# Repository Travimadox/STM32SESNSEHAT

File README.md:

# Imperium Environmental Monitoring HAT

The Imperium Environmental Monitoring HAT is a cutting-edge hardware accessory designed for use with STM32 microcontrollers. It is tailored for environmental monitoring and equipped with high-precision sensors for temperature and light. This allows for accurate data collection in various applications, including weather monitoring, room temperature monitoring, and greenhouse monitoring, providing invaluable insights into environmental conditions.

## Features

- High-precision sensors for temperature, humidity, atmospheric pressure, and light
- Seamlessly integrates into various systems
- Customizable to fit the needs of each user
- Easily programmable for extra functionality
- Affordable and reliable

## Usage

The Imperium Environmental Monitoring HAT can be used for a variety of purposes, including:

- Weather monitoring
- Room temperature and humidity monitoring
- Greenhouse monitoring

In addition, the sensor data can be used to make critical decisions about controlling external devices, such as triggering a fan or heater, to maintain a comfortable environment.

## Getting Started

To get started with the Imperium Environmental Monitoring HAT, simply connect it to your STM32 microcontroller using the provided pins. Then, download our library and follow the included instructions to begin collecting data.
- Hello World version of our board can be found here: [Hello World](HELLOWORLD.md)
- Detailed set-up instructions can be found here: [Setup](SESNSEHATSETUP.md)

## Customization

The Imperium Environmental Monitoring HAT is easily programmable, allowing the end user to add extra functionality to suit their specific needs. The provided libraries in the firmware folder includes examples of how to use the sensors.

## Cost

At Imperium, we pride ourselves on providing innovative and cost-effective solutions. Our HAT is a reliable and affordable option for anyone looking to monitor and control environmental conditions, whether in a commercial or personal setting.

## Support

If you have any questions or issues with the Imperium Environmental Monitoring HAT, please contact our support team at imperiumuct@gmail.com.

## License

This project is licensed under the [MIT License](LICENSE).

© 2023 Rumbizdai Mashumba, Phomolo Makina, and Travimadox Webb.

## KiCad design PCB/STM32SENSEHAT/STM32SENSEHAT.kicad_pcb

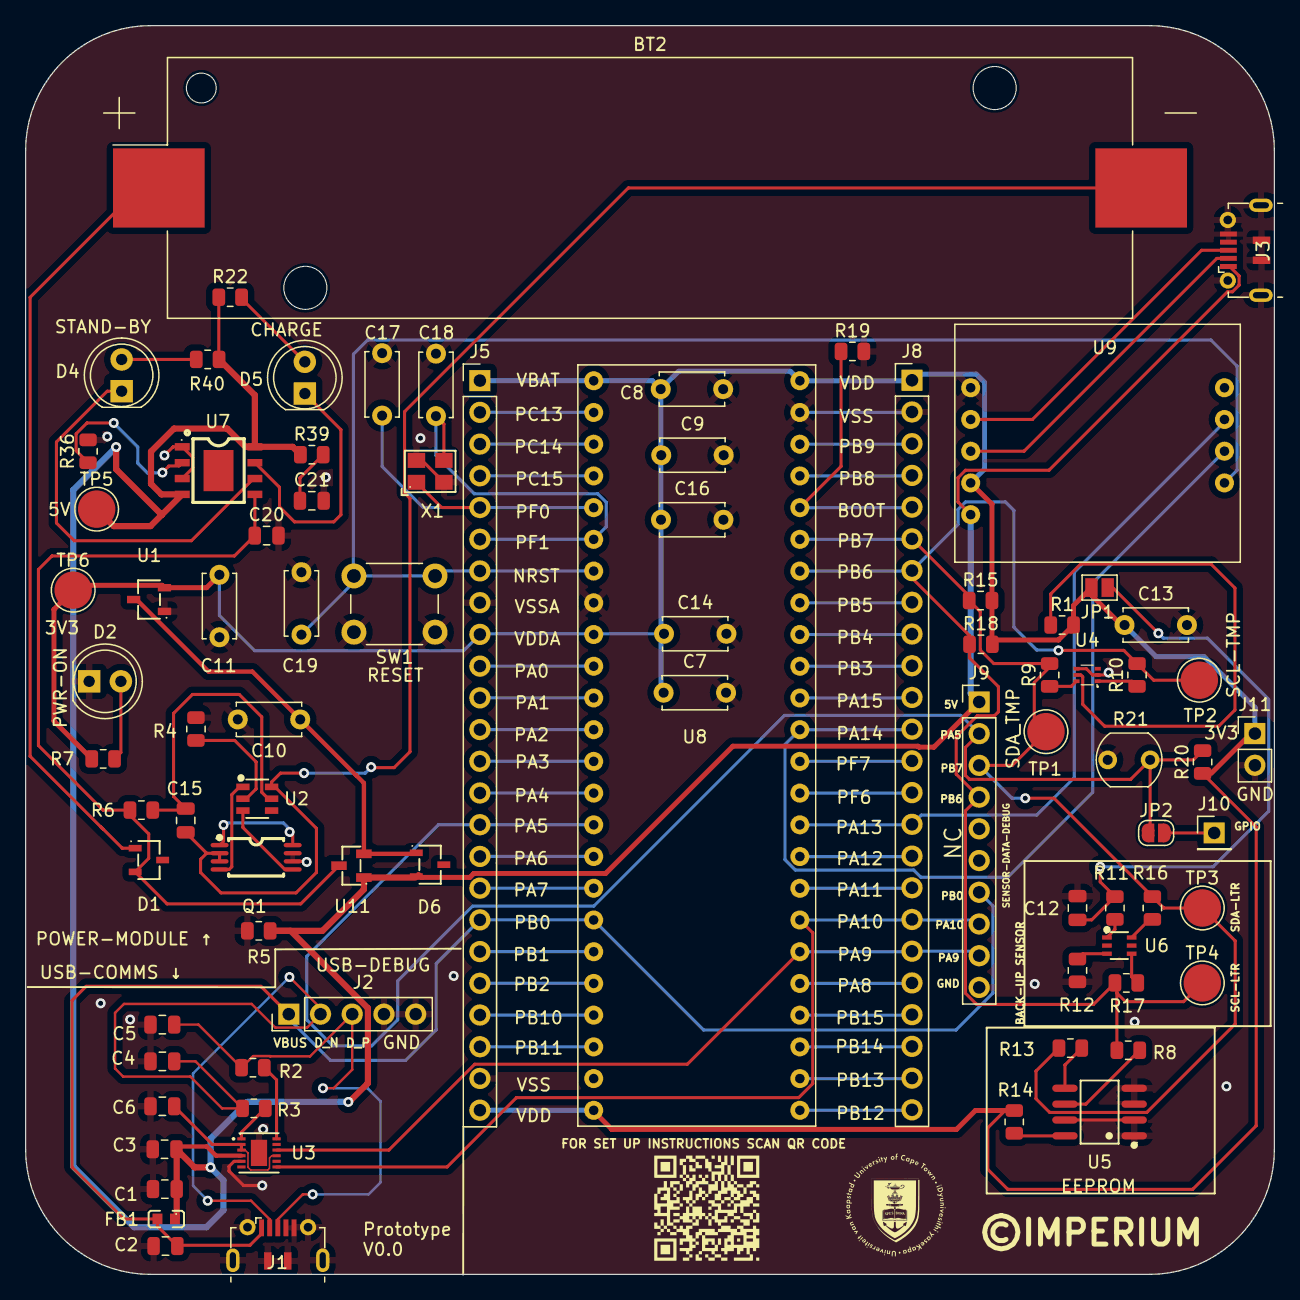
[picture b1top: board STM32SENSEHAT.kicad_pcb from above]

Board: 2 copper layers, 100.0 x 100.0 mm, 82 parts (0 on the bottom side), 78 nets.

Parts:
BT2: Battery_Cell; BatteryHolder_Keystone_1042_1x18650
C1, C6, C15: 100nF; C_0805_2012Metric
C2: 10nF; C_0805_2012Metric
C3: 4.7uF; C_0805_2012Metric
C4, C5: 47pF; C_0805_2012Metric
C7, C10, C11: 1uF; C_Disc_D5.0mm_W2.5mm_P5.00mm
C8, C9, C19: 100nF; C_Disc_D5.0mm_W2.5mm_P5.00mm
C12: 1uF; C_0805_2012Metric
C13, C14: 10nF; C_Disc_D5.0mm_W2.5mm_P5.00mm
C16: 4.7uF; C_Disc_D5.0mm_W2.5mm_P5.00mm
C17, C18: 10pF; C_Disc_D5.0mm_W2.5mm_P5.00mm
C20, C21: 10uF; C_0805_2012Metric
D1, D6: D_Schottky; SOT-23-3_L3.0-W1.7-P0.95-LS2.9-BR
D2, D4, D5: LED; LED_D5.0mm
FB1: FerriteBead; L0603
J1, J3: USB_B_Micro; USB_Conn_JLC_LCSC_C404969
J2: Conn_01x05_Pin; PinHeader_1x05_P2.54mm_Vertical
J5, J8: Conn_01x24_Pin; PinHeader_1x24_P2.54mm_Vertical
J9: Conn_01x10_Pin; PinHeader_1x10_P2.54mm_Vertical
J10: Conn_01x01_Pin; PinHeader_1x01_P2.54mm_Vertical
J11: Conn_01x02_Pin; PinHeader_1x02_P2.54mm_Vertical
JP1: SolderJumper_2_Open; SolderJumper-2_P1.3mm_Open_Pad1.0x1.5mm
JP2: SolderJumper_2_Open; SolderJumper-2_P1.3mm_Open_RoundedPad1.0x1.5mm
Q1: FS8205A; TSSOP-8_L4.4-W3.0-P0.65-LS6.4-BL
R1, R8, R9, R10, R11, R12, R13, R14, R16, R17, R39: 0R; R_0805_2012Metric
R2, R3: 27R; R_0805_2012Metric
R4, R7, R22, R40: 1k0; R_0805_2012Metric
R5, R19, R20, R36: 10k; R_0805_2012Metric
R6: 100R; R_0805_2012Metric
R15, R18: 4k7; R_0805_2012Metric
R21: LDR07; R_LDR_5.1x4.3mm_P3.4mm_Vertical
SW1: SW_Push; SW_PUSH_6mm
TP1, TP2, TP3, TP4, TP5, TP6: TestPoint; TestPoint_Pad_D3.0mm
U1: MCP1700x-330xxTT; SOT-23-3_L2.9-W1.6-P1.90-LS2.8-BR
U2: DW01A; SOT-23-6_L2.9-W1.6-P0.95-LS2.8-BL
U3: FT234XD-R; DFN-12_L3.0-W3.0-P0.45-BL-EP
U4: TMP102xxDRL; SOT-563_L1.6-W1.2-P0.50-LS1.6-BR
U5: CAT24C256; SOIC-8_L4.9-W3.9-P1.27-LS6.0-BL
U6: LTR-303ALS-01; SOT-363_L2.0-W1.3-P0.65-LS2.1-BL
U7: TP4056; ESOP-8_L4.9-W3.9-P1.27-LS6.0-BL-EP
U8: STM32F051C6T6
U9: STLINK_UCT
U11: AO3401A_C306862; SOT-23-3_L2.9-W1.3-P1.90-LS2.4-BR
X1: XXDCELNANF-8MHZ; OSC-SMD_4P-L3.2-W2.5-BL

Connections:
3V3: C7.1, C8.1, C9.1, C11.1, C13.1, C14.1, C16.1, J5.1, J5.9, J5.24, J8.1, J11.1, JP1.2 (B), R1.2, R7.1, R14.1, R15.2, R18.2, R20.1, TP6.1, U1.2 (VO), U8.1 (VBAT), U8.9 (V+), U8.24 (V+), U8.48 (V+), U9.2 (V_Target)
5VUSB: C1.1, C3.1, D6.2 (A), FB1.1, J3.1 (VBUS), J9.1, R5.1, R22.1, R39.1, R40.1, TP5.1, U3.4 (VCC), U7.4 (VCC), U7.8 (CE), U9.1 (5V_USB), U11.1 (G)
/MCU MODULE/BOOT: J8.5, R19.1, U8.44 (BOOT)
/MCU MODULE/NRST: C19.1, J5.7, SW1.2, U8.7 (NRST), U9.6 (T_NRST)
/MCU MODULE/PA0: J5.10, U8.10 (PA0)
/MCU MODULE/PA1: J5.11, U8.11 (PA1)
/MCU MODULE/PA2: J5.12, U8.12 (PA2)
/MCU MODULE/PA3: J5.13, U8.13 (PA3)
/MCU MODULE/PA4: J5.14, U8.14 (PA4)
/MCU MODULE/PA5: J5.15, J9.2, JP2.1 (A), R20.2, R21.1, U8.15 (PA5)
/MCU MODULE/PA6: J5.16, U8.16 (PA6)
/MCU MODULE/PA7: J5.17, U8.17 (PA7)
/MCU MODULE/PA8: J8.20, U8.29 (PA8)
/MCU MODULE/PA9: J8.19, J9.9, U3.10 (RXD), U8.30 (PA9)
/MCU MODULE/PA10: J8.18, J9.8, U3.7 (TXD), U8.31 (PA10)
/MCU MODULE/PA11: J8.17, U8.32 (PA11)
/MCU MODULE/PA12: J8.16, U8.33 (PA12)
/MCU MODULE/PA13: J8.15, U8.34 (PA13), U9.8 (T_SWDIO)
/MCU MODULE/PA14: J8.12, U8.37 (PA14), U9.7 (T_SWCLK)
/MCU MODULE/PA15: J8.11, U8.38 (PA15)
/MCU MODULE/PB0: C2.1, FB1.2, J1.1 (VBUS), J2.1, J5.18, J9.7, U8.18 (PB0)
/MCU MODULE/PB1: J5.19, U8.19 (PB1)
/MCU MODULE/PB2: J5.20, U8.20 (PB2)
/MCU MODULE/PB3: J8.10, U8.39 (PB3)
/MCU MODULE/PB4: J8.9, U8.40 (PB4)
/MCU MODULE/PB5: J8.8, U8.41 (PB5)
/MCU MODULE/PB6: J8.7, J9.4, R8.2, R10.2, R17.2, R18.1, TP2.1, TP4.1, U8.42 (PB6)
/MCU MODULE/PB7: J8.6, J9.3, R9.2, R13.1, R15.1, R16.2, TP1.1, TP3.1, U8.43 (PB7)
/MCU MODULE/PB8: J8.4, U8.45 (PB8)
/MCU MODULE/PB9: J8.3, U8.46 (PB9)
/MCU MODULE/PB10: J5.21, U8.21 (PB10)
/MCU MODULE/PB11: J5.22, U8.22 (PB11)
/MCU MODULE/PB12: J8.24, U8.25 (PB12)
/MCU MODULE/PB13: J8.23, U8.26 (PB13)
/MCU MODULE/PB14: J8.22, U8.27 (PB14)
/MCU MODULE/PB15: J8.21, U8.28 (PB15)
/MCU MODULE/PC13: J5.2, U8.2 (PC13)
/MCU MODULE/PC14: J5.3, U8.3 (PC14)
/MCU MODULE/PC15: J5.4, U8.4 (PC15)
/MCU MODULE/PF0: C17.1, J5.5, U8.5 (PF0), X1.1 (OE#)
/MCU MODULE/PF1: C18.1, J5.6, U8.6 (PF1), X1.3 (OUT)
/MCU MODULE/PF6: J8.14, U8.35 (PF6)
/MCU MODULE/PF7: J8.13, U8.36 (PF7)
/MCU MODULE/USB_DN: C4.1, J1.2 (D-), J2.2, R3.1
/MCU MODULE/USB_DP: C5.1, J1.3 (D+), J2.3, R2.1
/POWER MANAGEMENT MODULE/BATT+: C20.1, D1.2 (A), R6.2, U7.5 (BAT), U11.3 (D)
/POWER MANAGEMENT MODULE/LOAD_PWR: C10.1, D6.1 (K), U1.3 (VI), U11.2 (S)
/POWER MANAGEMENT MODULE/PROG: R36.1, U7.2 (PROG)
GND: C1.2, C2.2, C3.2, C4.2, C5.2, C6.2, C7.2, C8.2, C9.2, C10.2, C11.2, C12.2, C13.2, C14.2, C16.2, C17.2, C18.2, C19.2, C20.2, C21.2, D2.1 (K), J1.4 (ID), J1.5 (GND), J1.6 (Shield), J2.4, J2.5, J3.4 (ID), J3.5 (GND), J3.6 (Shield), J5.8, J5.23, J8.2, J9.10, J11.2, Q1.6, Q1.7, R4.2, R5.2, R12.1, R19.2, R21.2, R36.2, SW1.1, U1.1 (GND), U3.5 (GND), U3.13 (GND), U4.2 (GND), U4.4 (ADD0), U5.1 (A0), U5.2 (A1), U5.3 (A2), U5.4 (GND), U5.7 (WP), U7.1 (TEMP), U7.3 (GND), U8.8 (GND), U8.23 (GND), U8.47 (GND), U9.5 (GND), X1.2 (GND), X1.4 (GND)
unnamed: BT2.1 (+), D1.1 (K)
unnamed: BT2.2 (-), C15.2, Q1.2, Q1.3, U2.6 (GND)
unnamed: C21.1, R39.2
unnamed: D2.2 (A), R7.2
unnamed: D4.2 (A), R40.2
unnamed: D4.1 (K), U7.6 (!STDBY)
unnamed: D5.2 (A), R22.2
unnamed: D5.1 (K), U7.7 (!CHRG)
unnamed: J3.3 (D+), U9.4 (USB_DP)
unnamed: J3.2 (D-), U9.3 (USB_DM)
unnamed: J10.1, JP2.2 (B)
unnamed: C12.1, JP1.1 (A), R11.2
unnamed: R4.1, U2.2 (CS)
unnamed: Q1.5, U2.3 (OC)
unnamed: Q1.4, U2.1 (OD)
unnamed: C15.1, R6.1, U2.5 (VDD)
unnamed: C6.1, U3.2 (~RESET#), U3.3 (3V3OUT), U3.9 (VCCIO)
unnamed: R3.2, U3.1 (USBDM)
unnamed: R2.2, U3.12 (USBDP)
unnamed: R10.1, U4.1 (SCL)
unnamed: R9.1, U4.6 (SDA)
unnamed: R1.1, U4.5 (V+)
unnamed: R8.1, U5.6 (SCL)
unnamed: R13.2, U5.5 (SDA)
unnamed: R14.2, U5.8 (VCC)
unnamed: R12.2, U6.3 (GND)
unnamed: R17.1, U6.4 (SCL)
unnamed: R16.1, U6.6 (SDA)
unnamed: R11.1, U6.1 (VDD)

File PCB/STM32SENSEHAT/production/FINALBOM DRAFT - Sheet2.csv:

Comment,Designator,Footprint,JLCPCB Part #
100nF,"C1, C6, C15",Capacitor_SMD:C_0805_2012Metric,C49678
10nF,C2,Capacitor_SMD:C_0805_2012Metric,C1710
4.7uF,C3,Capacitor_SMD:C_0805_2012Metric,C1779
47pF,"C4, C5",Capacitor_SMD:C_0805_2012Metric,C14857
1uF,C12,Capacitor_SMD:C_0805_2012Metric,C28323
10uF,"C20, C21",Capacitor_SMD:C_0805_2012Metric,C15850
D_Schottky,"D1, D6",JLCfootprint:SOT-23-3_L3.0-W1.7-P0.95-LS2.9-BR,C47546
FerriteBead,FB1,JLCfootprint:L0603,C13415
USB_B_Micro,J1,footprints:USB_Conn_JLC_LCSC_C404969,C404969
FS8205A,Q1,JLCfootprint:TSSOP-8_L4.4-W3.0-P0.65-LS6.4-BL,C306862
0R,"R1, R8-R14, R16, R17, R39",Resistor_SMD:R_0805_2012Metric,C17477
27R,"R2, R3",Resistor_SMD:R_0805_2012Metric,C17594
1k0,"R4, R7, R40",Resistor_SMD:R_0805_2012Metric,C17513
10k,"R5, R19, R20, R36",Resistor_SMD:R_0805_2012Metric,C17414
100R,R6,Resistor_SMD:R_0805_2012Metric,C17408
4k7,"R15, R18",Resistor_SMD:R_0805_2012Metric,C17673
MCP1700x-330xxTT,U1,JLCfootprint:SOT-23-3_L2.9-W1.6-P1.90-LS2.8-BR,C39051
DW01A,U2,JLCfootprint:SOT-23-6_L2.9-W1.6-P0.95-LS2.8-BL,C351410
FT234XD-R,U3,JLCfootprint:DFN-12_L3.0-W3.0-P0.45-BL-EP,C132158
TMP102xxDRL,U4,JLCfootprint:SOT-563_L1.6-W1.2-P0.50-LS1.6-BR,C99269
CAT24C256,U5,JLCfootprint:SOIC-8_L4.9-W3.9-P1.27-LS6.0-BL,C6482
LTR-303ALS-01,U6,JLCfootprint:SOT-363_L2.0-W1.3-P0.65-LS2.1-BL,C364577
TP4056,U7,JLCfootprint:ESOP-8_L4.9-W3.9-P1.27-LS6.0-BL-EP,C382139
AO3401A_C306862,U11,JLCfootprint:SOT-23-3_L2.9-W1.3-P1.90-LS2.4-BR,C306862
XXDCELNANF-8MHZ,X1,JLCfootprint:OSC-SMD_4P-L3.2-W2.5-BL,C367183

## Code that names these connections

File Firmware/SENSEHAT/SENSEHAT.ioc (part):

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Mcu.Name=STM32F051C6Tx
Mcu.Package=LQFP48
Mcu.UserName=STM32F051C6Tx
PA10.Mode=Asynchronous
PA10.Signal=USART1_RX
PA5.Mode=IN5
PA5.Signal=ADC_IN5
PA9.Mode=Asynchronous
PA9.Signal=USART1_TX
PB2.GPIOParameters=GPIO_PuPd
PB2.GPIO_PuPd=GPIO_PULLDOWN
PB2.Signal=GPIO_Input
PB6.Mode=I2C
PB6.Signal=I2C1_SCL
PB7.Mode=I2C
PB7.Signal=I2C1_SDA
PC14-OSC32_IN.Mode=LSE-External-Oscillator
PC14-OSC32_IN.Signal=RCC_OSC32_IN
PC15-OSC32_OUT.Mode=LSE-External-Oscillator
PC15-OSC32_OUT.Signal=RCC_OSC32_OUT
PF0-OSC_IN.Mode=HSE-External-Oscillator
PF0-OSC_IN.Signal=RCC_OSC_IN
PF1-OSC_OUT.Mode=HSE-External-Oscillator
PF1-OSC_OUT.Signal=RCC_OSC_OUT
RCC.SYSCLKFreq_VALUE=48000000
RCC.SYSCLKSource=RCC_SYSCLKSOURCE_PLLCLK
board=custom

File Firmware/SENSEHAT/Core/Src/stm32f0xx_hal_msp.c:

/* USER CODE BEGIN Header */
/**
  ******************************************************************************
  * @file         stm32f0xx_hal_msp.c
  * @brief        This file provides code for the MSP Initialization
  *               and de-Initialization codes.
  ******************************************************************************
  * @attention
  *
  * Copyright (c) 2023 STMicroelectronics.
  * All rights reserved.
  *
  * This software is licensed under terms that can be found in the LICENSE file
  * in the root directory of this software component.
  * If no LICENSE file comes with this software, it is provided AS-IS.
  *
  ******************************************************************************
  */
/* USER CODE END Header */

/* Includes ------------------------------------------------------------------*/
#include "main.h"
/* USER CODE BEGIN Includes */

/* USER CODE END Includes */

/* Private typedef -----------------------------------------------------------*/
/* USER CODE BEGIN TD */

/* USER CODE END TD */

/* Private define ------------------------------------------------------------*/
/* USER CODE BEGIN Define */

/* USER CODE END Define */

/* Private macro -------------------------------------------------------------*/
/* USER CODE BEGIN Macro */

/* USER CODE END Macro */

/* Private variables ---------------------------------------------------------*/
/* USER CODE BEGIN PV */

/* USER CODE END PV */

/* Private function prototypes -----------------------------------------------*/
/* USER CODE BEGIN PFP */

/* USER CODE END PFP */

/* External functions --------------------------------------------------------*/
/* USER CODE BEGIN ExternalFunctions */

/* USER CODE END ExternalFunctions */

/* USER CODE BEGIN 0 */

/* USER CODE END 0 */
/**
  * Initializes the Global MSP.
  */
void HAL_MspInit(void)
{
  /* USER CODE BEGIN MspInit 0 */

  /* USER CODE END MspInit 0 */

  __HAL_RCC_SYSCFG_CLK_ENABLE();
  __HAL_RCC_PWR_CLK_ENABLE();

  /* System interrupt init*/

  /* USER CODE BEGIN MspInit 1 */

  /* USER CODE END MspInit 1 */
}

/**
* @brief ADC MSP Initialization
* This function configures the hardware resources used in this example
* @param hadc: ADC handle pointer
* @retval None
*/
void HAL_ADC_MspInit(ADC_HandleTypeDef* hadc)
{
  GPIO_InitTypeDef GPIO_InitStruct = {0};
  if(hadc->Instance==ADC1)
  {
  /* USER CODE BEGIN ADC1_MspInit 0 */

  /* USER CODE END ADC1_MspInit 0 */
    /* Peripheral clock enable */
    __HAL_RCC_ADC1_CLK_ENABLE();

    __HAL_RCC_GPIOA_CLK_ENABLE();
    /**ADC GPIO Configuration
    PA5     ------> ADC_IN5
    */
    GPIO_InitStruct.Pin = GPIO_PIN_5;
    GPIO_InitStruct.Mode = GPIO_MODE_ANALOG;
    GPIO_InitStruct.Pull = GPIO_NOPULL;
    HAL_GPIO_Init(GPIOA, &GPIO_InitStruct);

  /* USER CODE BEGIN ADC1_MspInit 1 */

  /* USER CODE END ADC1_MspInit 1 */
  }

}

/**
* @brief ADC MSP De-Initialization
* This function freeze the hardware resources used in this example
* @param hadc: ADC handle pointer
* @retval None
*/
void HAL_ADC_MspDeInit(ADC_HandleTypeDef* hadc)
{
  if(hadc->Instance==ADC1)
  {
  /* USER CODE BEGIN ADC1_MspDeInit 0 */

  /* USER CODE END ADC1_MspDeInit 0 */
    /* Peripheral clock disable */
    __HAL_RCC_ADC1_CLK_DISABLE();

    /**ADC GPIO Configuration
    PA5     ------> ADC_IN5
    */
    HAL_GPIO_DeInit(GPIOA, GPIO_PIN_5);

  /* USER CODE BEGIN ADC1_MspDeInit 1 */

  /* USER CODE END ADC1_MspDeInit 1 */
  }

}

/**
* @brief I2C MSP Initialization
* This function configures the hardware resources used in this example
* @param hi2c: I2C handle pointer
* @retval None
*/
void HAL_I2C_MspInit(I2C_HandleTypeDef* hi2c)
{
  GPIO_InitTypeDef GPIO_InitStruct = {0};
  if(hi2c->Instance==I2C1)
  {
  /* USER CODE BEGIN I2C1_MspInit 0 */

  /* USER CODE END I2C1_MspInit 0 */

    __HAL_RCC_GPIOB_CLK_ENABLE();
    /**I2C1 GPIO Configuration
    PB8     ------> I2C1_SCL
    PB9     ------> I2C1_SDA
    */
    GPIO_InitStruct.Pin = GPIO_PIN_8|GPIO_PIN_9;
    GPIO_InitStruct.Mode = GPIO_MODE_AF_OD;
    GPIO_InitStruct.Pull = GPIO_NOPULL;
    GPIO_InitStruct.Speed = GPIO_SPEED_FREQ_HIGH;
    GPIO_InitStruct.Alternate = GPIO_AF1_I2C1;
    HAL_GPIO_Init(GPIOB, &GPIO_InitStruct);

    /* Peripheral clock enable */
    __HAL_RCC_I2C1_CLK_ENABLE();
  /* USER CODE BEGIN I2C1_MspInit 1 */

  /* USER CODE END I2C1_MspInit 1 */
  }

}

/**
* @brief I2C MSP De-Initialization
* This function freeze the hardware resources used in this example
* @param hi2c: I2C handle pointer
* @retval None
*/
void HAL_I2C_MspDeInit(I2C_HandleTypeDef* hi2c)
{
  if(hi2c->Instance==I2C1)
  {
  /* USER CODE BEGIN I2C1_MspDeInit 0 */

  /* USER CODE END I2C1_MspDeInit 0 */
    /* Peripheral clock disable */
    __HAL_RCC_I2C1_CLK_DISABLE();

    /**I2C1 GPIO Configuration
    PB8     ------> I2C1_SCL
    PB9     ------> I2C1_SDA
    */
    HAL_GPIO_DeInit(GPIOB, GPIO_PIN_8);

    HAL_GPIO_DeInit(GPIOB, GPIO_PIN_9);

  /* USER CODE BEGIN I2C1_MspDeInit 1 */

  /* USER CODE END I2C1_MspDeInit 1 */
  }

}

/**
* @brief RTC MSP Initialization
* This function configures the hardware resources used in this example
* @param hrtc: RTC handle pointer
* @retval None
*/
void HAL_RTC_MspInit(RTC_HandleTypeDef* hrtc)
{
  if(hrtc->Instance==RTC)
  {
  /* USER CODE BEGIN RTC_MspInit 0 */

  /* USER CODE END RTC_MspInit 0 */
    /* Peripheral clock enable */
    __HAL_RCC_RTC_ENABLE();
  /* USER CODE BEGIN RTC_MspInit 1 */

  /* USER CODE END RTC_MspInit 1 */
  }

}

/**
* @brief RTC MSP De-Initialization
* This function freeze the hardware resources used in this example
* @param hrtc: RTC handle pointer
* @retval None
*/
void HAL_RTC_MspDeInit(RTC_HandleTypeDef* hrtc)
{
  if(hrtc->Instance==RTC)
  {
  /* USER CODE BEGIN RTC_MspDeInit 0 */

  /* USER CODE END RTC_MspDeInit 0 */
    /* Peripheral clock disable */
    __HAL_RCC_RTC_DISABLE();
  /* USER CODE BEGIN RTC_MspDeInit 1 */

  /* USER CODE END RTC_MspDeInit 1 */
  }

}

/**
* @brief TIM_Base MSP Initialization
* This function configures the hardware resources used in this example
* @param htim_base: TIM_Base handle pointer
* @retval None
*/
void HAL_TIM_Base_MspInit(TIM_HandleTypeDef* htim_base)
{
  if(htim_base->Instance==TIM2)
  {
  /* USER CODE BEGIN TIM2_MspInit 0 */

  /* USER CODE END TIM2_MspInit 0 */
    /* Peripheral clock enable */
    __HAL_RCC_TIM2_CLK_ENABLE();
    /* TIM2 interrupt Init */
    HAL_NVIC_SetPriority(TIM2_IRQn, 0, 0);
    HAL_NVIC_EnableIRQ(TIM2_IRQn);
  /* USER CODE BEGIN TIM2_MspInit 1 */

  /* USER CODE END TIM2_MspInit 1 */
  }

}

/**
* @brief TIM_Base MSP De-Initialization
* This function freeze the hardware resources used in this example
* @param htim_base: TIM_Base handle pointer
* @retval None
*/
void HAL_TIM_Base_MspDeInit(TIM_HandleTypeDef* htim_base)
{
  if(htim_base->Instance==TIM2)
  {
  /* USER CODE BEGIN TIM2_MspDeInit 0 */

  /* USER CODE END TIM2_MspDeInit 0 */
    /* Peripheral clock disable */
    __HAL_RCC_TIM2_CLK_DISABLE();

    /* TIM2 interrupt DeInit */
    HAL_NVIC_DisableIRQ(TIM2_IRQn);
  /* USER CODE BEGIN TIM2_MspDeInit 1 */

  /* USER CODE END TIM2_MspDeInit 1 */
  }

}

/**
* @brief UART MSP Initialization
* This function configures the hardware resources used in this example
* @param huart: UART handle pointer
* @retval None
*/
void HAL_UART_MspInit(UART_HandleTypeDef* huart)
{
  GPIO_InitTypeDef GPIO_InitStruct = {0};
  if(huart->Instance==USART1)
  {
  /* USER CODE BEGIN USART1_MspInit 0 */

  /* USER CODE END USART1_MspInit 0 */
    /* Peripheral clock enable */
    __HAL_RCC_USART1_CLK_ENABLE();

    __HAL_RCC_GPIOA_CLK_ENABLE();
    /**USART1 GPIO Configuration
    PA9     ------> USART1_TX
    PA10     ------> USART1_RX
    */
    GPIO_InitStruct.Pin = GPIO_PIN_9|GPIO_PIN_10;
    GPIO_InitStruct.Mode = GPIO_MODE_AF_PP;
    GPIO_InitStruct.Pull = GPIO_NOPULL;
    GPIO_InitStruct.Speed = GPIO_SPEED_FREQ_HIGH;
    GPIO_InitStruct.Alternate = GPIO_AF1_USART1;
    HAL_GPIO_Init(GPIOA, &GPIO_InitStruct);

  /* USER CODE BEGIN USART1_MspInit 1 */

  /* USER CODE END USART1_MspInit 1 */
  }

}

/**
* @brief UART MSP De-Initialization
* This function freeze the hardware resources used in this example
* @param huart: UART handle pointer
* @retval None
*/
void HAL_UART_MspDeInit(UART_HandleTypeDef* huart)
{
  if(huart->Instance==USART1)
  {
  /* USER CODE BEGIN USART1_MspDeInit 0 */

  /* USER CODE END USART1_MspDeInit 0 */
    /* Peripheral clock disable */
    __HAL_RCC_USART1_CLK_DISABLE();

    /**USART1 GPIO Configuration
    PA9     ------> USART1_TX
    PA10     ------> USART1_RX
    */
    HAL_GPIO_DeInit(GPIOA, GPIO_PIN_9|GPIO_PIN_10);

  /* USER CODE BEGIN USART1_MspDeInit 1 */

  /* USER CODE END USART1_MspDeInit 1 */
  }

}

/* USER CODE BEGIN 1 */

/* USER CODE END 1 */

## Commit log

2023-02-24 Add new directory
2023-02-24 BME280 Sensor Datasheet possible sensor selection
2023-02-24 Update README.md updated the support email
2023-02-25 Add new file
2023-02-25 Update License Information
2023-02-25 Updated license information
2023-02-28 Upload New File
2023-03-04 Sense hat Schematic First Iteration
2023-03-04 rework of top level sheet, MCU, power and sensor sheet
2023-03-04 BOM generated
2023-03-04 Modified the connector symbol for STM32 from 66 pins to 48 pins
2023-03-05 Add STM32SENSEHAT, power, sensor, and mcu schematic files
2023-03-05 Removed the extra sensor, Modified BME280 interfacing and FTDI UART pins. Added Manual Reset to MCU and configured BOOT pin
2023-03-05 Upload Sensehat BOM File
2023-03-06 Add STM32SENSEHAT, power, sensor, and mcu schematic file
2023-03-06 Rectified management spelling, added notes to sensor module and removed extra sensor's I2C pin
2023-03-08 Revised schematics. Moved USB and EEPROM sub modules to MCU sheet and and rectified the top sheet accordingly
2023-03-08 Added I2C,GPIO ports for the back up sesnors to the top level sheet
2023-03-08 Added extra set of male pin headers
2023-03-08 Added Battery Volatge Sesnsing capability
2023-03-08 Added an extra back up sensor(#LTR-303 ALS-01),Test points for I2C SDA and SCL and solder jumpers
2023-03-08 Removed STM32SENSEHAT-backups/STM32SENSEHAT-2023-03-04_114006.zip
2023-03-08 Removed STM32SENSEHAT-backups/STM32SENSEHAT-2023-03-04_115300.zip
2023-03-10 Protectuion features added to all schematica
2023-03-11 Schematics reviewed
2023-03-11 Schematics review top sheet
2023-03-12 Added footprints to the components but still pending review by Rumbizdai and Phomolo
2023-03-25 Rework of Power,MCU and Sensor Schematic
2023-03-25 PCB draft
2023-03-26 Changed the footprint of cpacitors C10 and C11 to C_disc"
2023-03-27 Changed TMP102 capacitor footprint to ceramic
2023-03-27 OScillator added
2023-03-27 Changed the value of the oscillator's capcitors to match the specified value in the datasheet
2023-03-27 Added capacitor paralle to NRST switch to mtigate parasitic effects
2023-03-27 Uploaded datasheets for chips in schematic
2023-03-27 MCU datasheet
2023-03-28 New PCB with tracks laid
2023-03-28 Slight PCB changes
2023-03-28 Added a poer indicator LED and rectified NRST parastic capacitance
2023-03-28 Updated PCB with latest changes
2023-03-28 Final draft pending review
2023-03-29 Gerber files and postion files generated
2023-03-29 JLC ready BOm draft
2023-03-31 Changed the QR Code on PCB
2023-03-31 Changed the Oscillator to C518154 cause of low stock
2023-04-01 Deleted old production files
2023-04-01 updated PCB
2023-04-03 Cleaned up Production Files
2023-04-03 Deleted production files
2023-04-04 Rectified error on FS8205A and AO3401
2023-04-04 Final production file
2023-04-12 Added Justin's Feedback
2023-04-13 Modified production files
2023-04-13 Modified BOM
2023-04-13 Modified production files gerber files
2023-05-06 First draft of TMP102 Library
2023-05-06 Added Library files for LDR but yet to tested
2023-05-06 Instructions on how to use the LDR files
2023-05-06 instructions on how to use the TMP102 library
2023-05-07 Draft report for the HAT
2023-05-07 Sensor data and rtc libraries uodate
2023-05-07 Updated the integration guides
2023-05-07 Modified rtc instructions file
2023-05-07 Added an example of how to use RTC
2023-05-07 Added Controllers TECH EEPROM Library
2023-05-08 Deleted information on the humidity and temperature sensor
2023-05-08 Added the initial drafts for the code dcoumentation for the sensor libraries
2023-05-08 Modified the EEPROM library
2023-05-08 Code reference for EEprom Library
2023-05-08 Rectified error on floattobytes function
2023-05-08 Test code for the libraries
2023-05-09 Deleted CAD and Simulation
2023-05-10 Add files via upload
    Illustrative instruction (images)
2023-05-10 Add files via upload
    Illustrative instructions
2023-05-10 Delete 20230509_231036[1].jpg
    Replacing the board image
2023-05-10 Add files via upload
    STM32 board image
2023-05-10 Delete STM32_board.jpg
    Replacing STM32 board the image with edited one
2023-05-10 Add files via upload
    Edited STM32 board image
2023-05-10 Delete STM32 board.png
    Deleted old STM32 board image
2023-05-10 Add files via upload
    New STM32 board image (jpg file)
2023-05-10 Update SESNSEHATSETUP.md
    Updated the SENSEHATSETUP instructions
2023-05-10 Add files via upload
    Debug_image
2023-05-10 Update SESNSEHATSETUP.md
    Added more steps on how to setup the SENSEHAT
2023-05-11 Update SESNSEHATSETUP.md
    Added run time message in step4
2023-05-11 Added getdate functionality
2023-05-11 Added date functionality
2023-05-11 Added RTCLIB Test
2023-05-11 Linked the STM32 Peripheral setup file
2023-05-12 Added requirements
2023-05-12 Update SESNSEHATSETUP.md
    Grammar correction
2023-05-12 Update README.md
    Grammar correction
2023-05-12 Update CONTRIBUTING.md
    Corrected Email address
2023-05-12 Added software emulators
2023-05-13 First iteration of integration code
2023-05-13 Added link to the stm32sensehat driver
2023-05-13 Added author and company data
2023-05-13 Final code reference
2023-05-13 Removed redundancies
2023-05-14 Non polling version
2023-05-16 Code reading reasonalble data now
2023-05-17 Demo working version
2023-05-26 Last change

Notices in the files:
PCB/STM32SENSEHAT/STM32SENSEHAT.kicad_pcb:
©IMPERIUM
